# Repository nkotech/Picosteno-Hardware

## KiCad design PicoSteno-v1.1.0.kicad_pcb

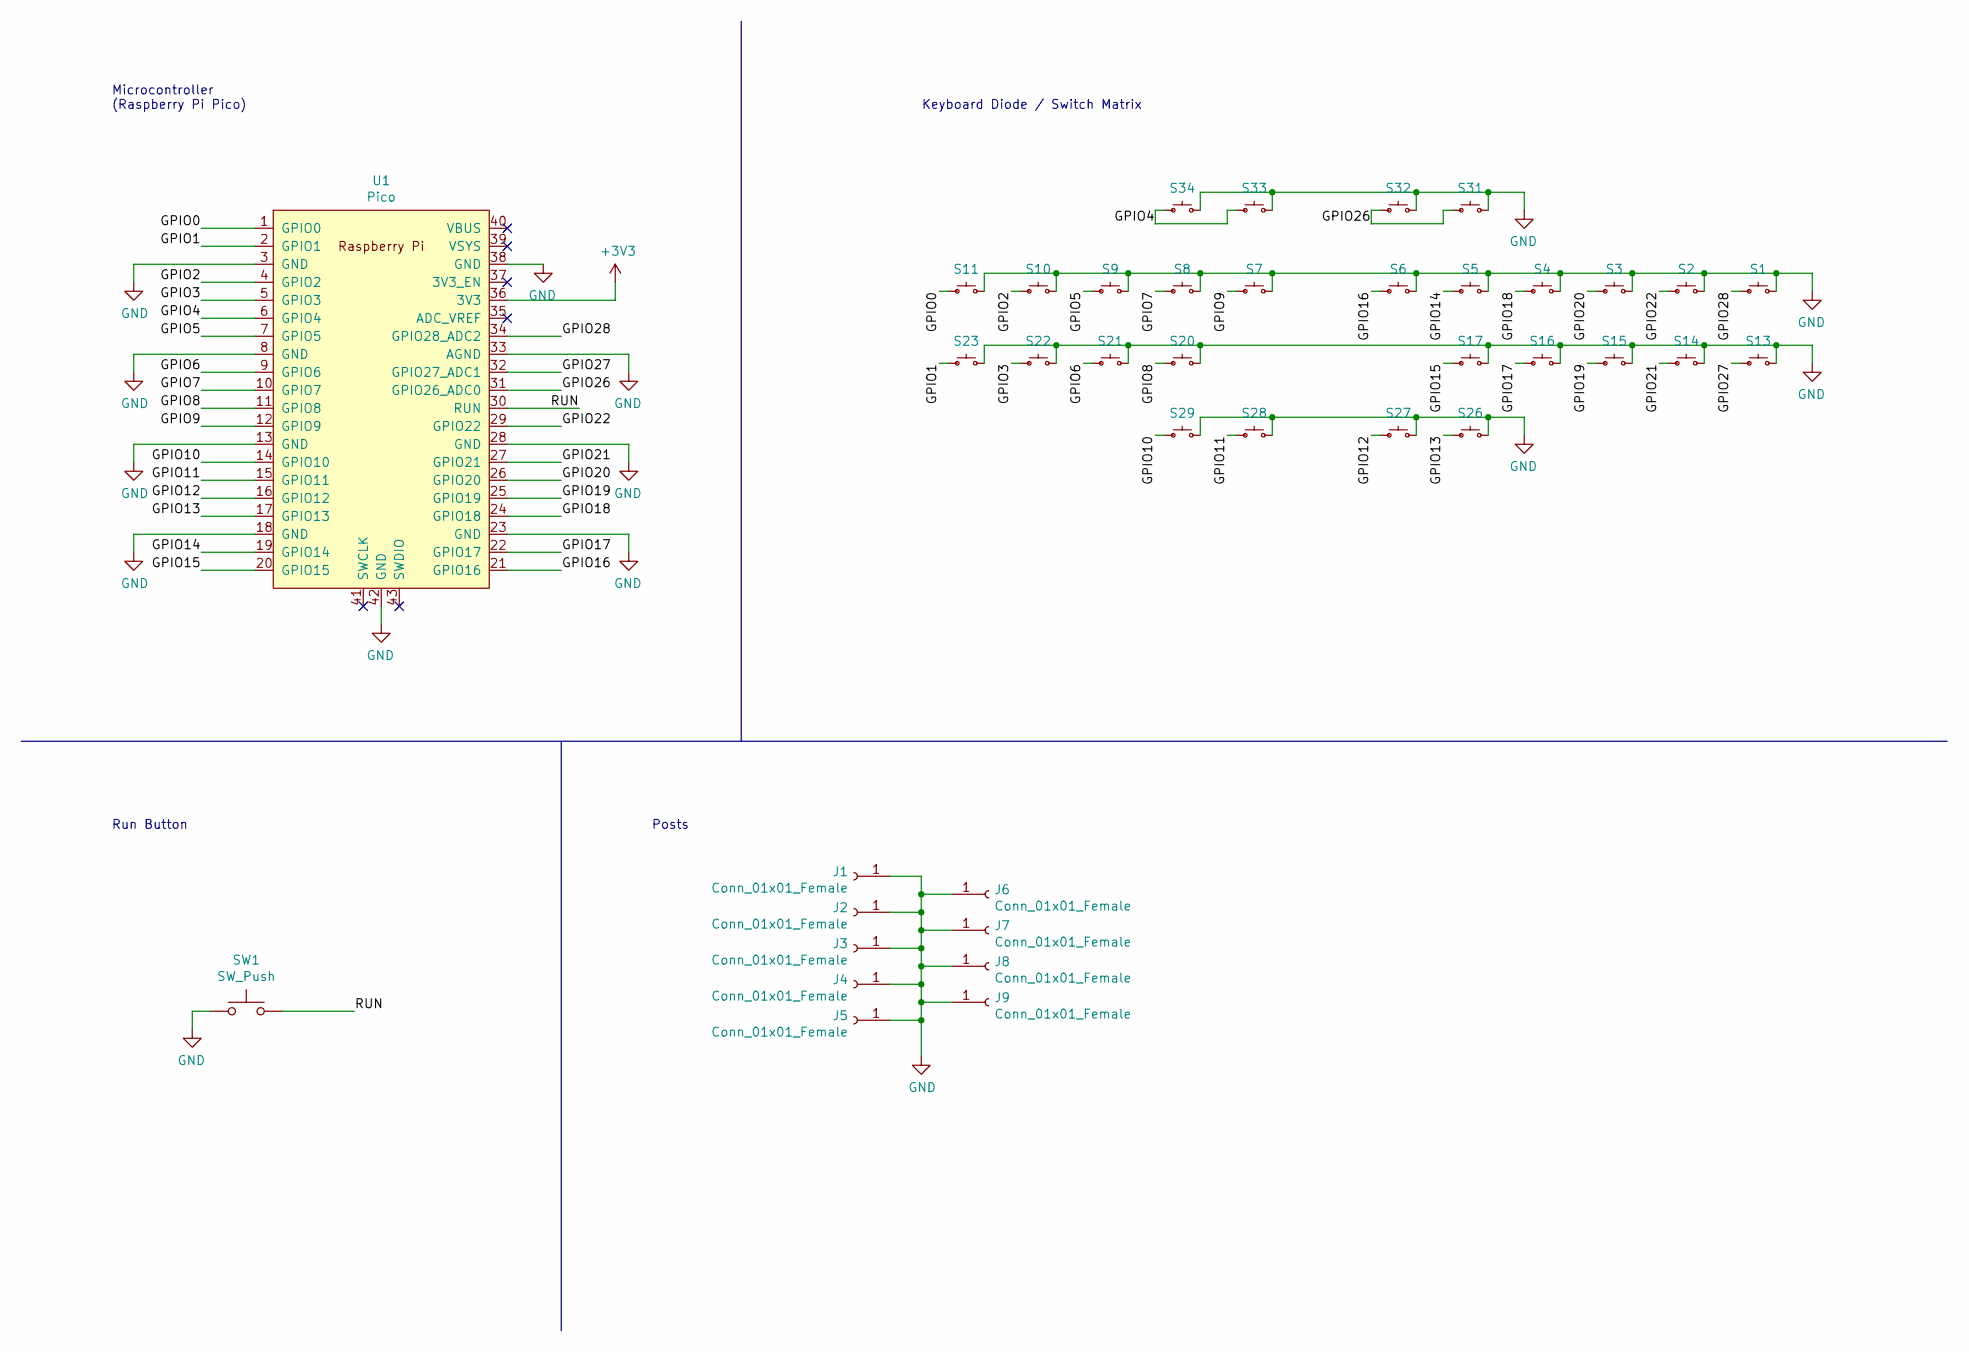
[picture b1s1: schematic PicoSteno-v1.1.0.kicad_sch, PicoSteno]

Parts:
J1, J2, J3, J4, J5, J6, J7, J8, J9: Conn_01x01_Female; Post
S1, S2, S3, S4, S5, S6, S7, S8, S9, S10, S11, S13, S14, S15, S16, S17, S20, S21, S22, S23, S26, S27, S28, S29, S31, S32, S33, S34: Kailh_Choc; Keyswitch_Kailh_Leadside_FrictionSnap
SW1: SW_Push; SW_PUSH_6mm
U1: Pico; RPi_Pico_SMD_TH

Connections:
+3V3: U1.36 (3V3)
/GPIO0: S11.1, U1.1 (GPIO0)
/GPIO1: S23.1, U1.2 (GPIO1)
/GPIO2: S10.1, U1.4 (GPIO2)
/GPIO3: S22.1, U1.5 (GPIO3)
/GPIO4: S33.1, S34.1, U1.6 (GPIO4)
/GPIO5: S9.1, U1.7 (GPIO5)
/GPIO6: S21.1, U1.9 (GPIO6)
/GPIO7: S8.1, U1.10 (GPIO7)
/GPIO8: S20.1, U1.11 (GPIO8)
/GPIO9: S7.1, U1.12 (GPIO9)
/GPIO10: S29.1, U1.14 (GPIO10)
/GPIO11: S28.1, U1.15 (GPIO11)
/GPIO12: S27.1, U1.16 (GPIO12)
/GPIO13: S26.1, U1.17 (GPIO13)
/GPIO14: S5.1, U1.19 (GPIO14)
/GPIO15: S17.1, U1.20 (GPIO15)
/GPIO16: S6.1, U1.21 (GPIO16)
/GPIO17: S16.1, U1.22 (GPIO17)
/GPIO18: S4.1, U1.24 (GPIO18)
/GPIO19: S15.1, U1.25 (GPIO19)
/GPIO20: S3.1, U1.26 (GPIO20)
/GPIO21: S14.1, U1.27 (GPIO21)
/GPIO22: S2.1, U1.29 (GPIO22)
/GPIO26: S31.1, S32.1, U1.31 (GPIO26_ADC0)
/GPIO27: S13.1, U1.32 (GPIO27_ADC1)
/GPIO28: S1.1, U1.34 (GPIO28_ADC2)
/RUN: SW1.2, U1.30 (RUN)
GND: J1.1, J2.1, J3.1, J4.1, J5.1, J6.1, J7.1, J8.1, J9.1, S1.2, S2.2, S3.2, S4.2, S5.2, S6.2, S7.2, S8.2, S9.2, S10.2, S11.2, S13.2, S14.2, S15.2, S16.2, S17.2, S20.2, S21.2, S22.2, S23.2, S26.2, S27.2, S28.2, S29.2, S31.2, S32.2, S33.2, S34.2, SW1.1, U1.3 (GND), U1.8 (GND), U1.13 (GND), U1.18 (GND), U1.23 (GND), U1.28 (GND), U1.33 (AGND), U1.38 (GND), U1.42 (GND)

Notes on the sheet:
Posts
Microcontroller (Raspberry Pi Pico)
Keyboard Diode / Switch Matrix
Run Button

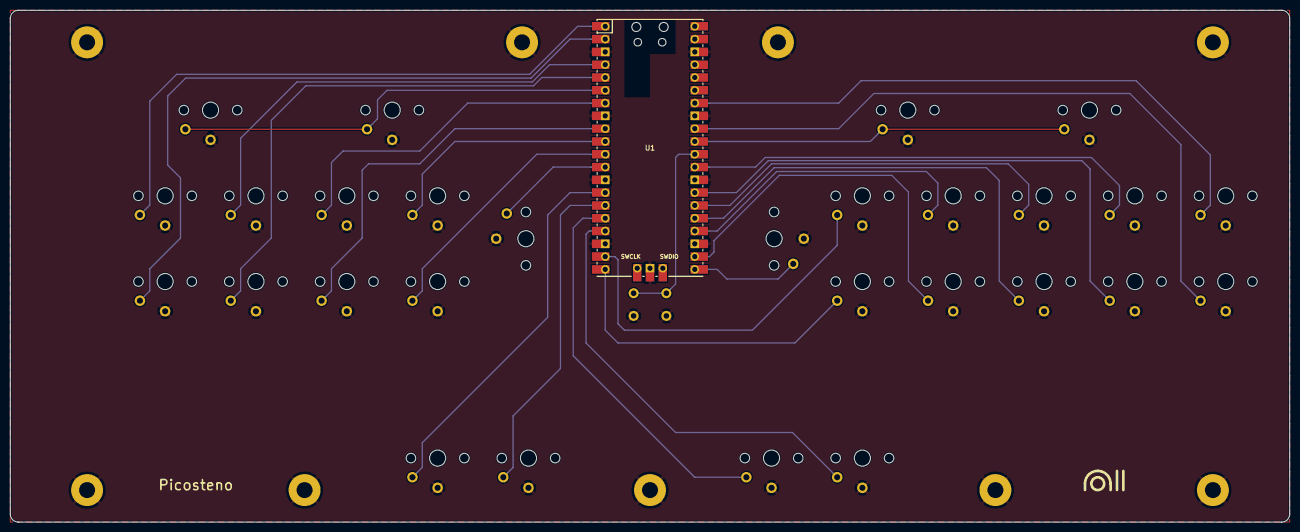
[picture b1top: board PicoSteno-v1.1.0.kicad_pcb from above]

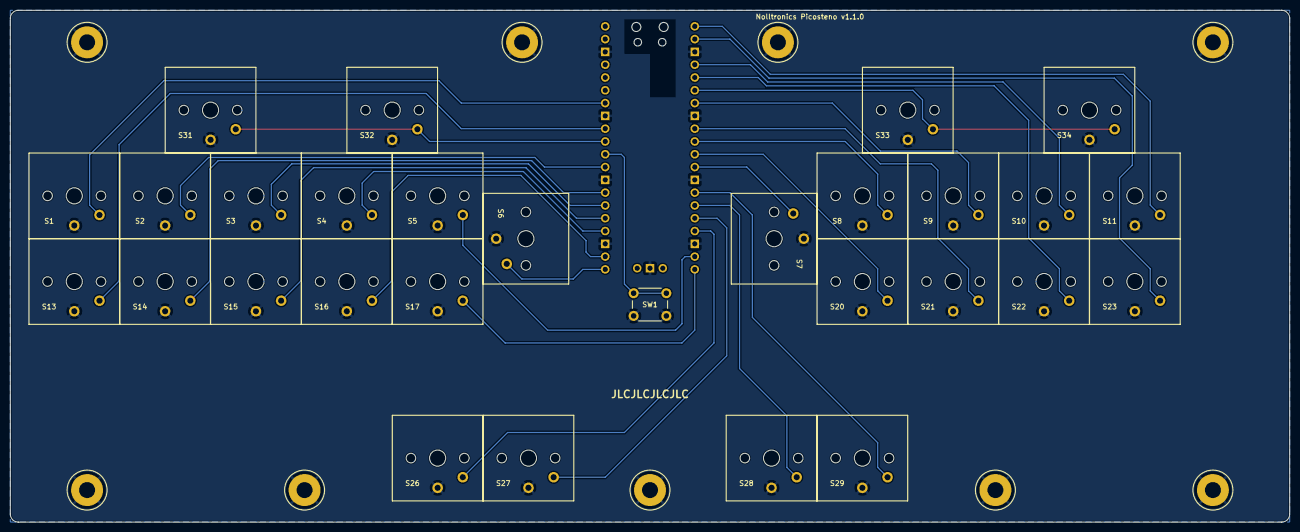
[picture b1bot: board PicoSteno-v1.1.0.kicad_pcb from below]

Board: 2 copper layers, 254.0 x 101.6 mm, 39 parts (29 on the bottom side), 28 nets.

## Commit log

2024-08-27 Initial Commit
    Picosteno hardware files
